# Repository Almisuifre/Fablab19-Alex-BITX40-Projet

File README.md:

# Fablab19-Alex-BITX40-Projet
Projet radio amateur fait au Fablab 19 - Création du BITX40

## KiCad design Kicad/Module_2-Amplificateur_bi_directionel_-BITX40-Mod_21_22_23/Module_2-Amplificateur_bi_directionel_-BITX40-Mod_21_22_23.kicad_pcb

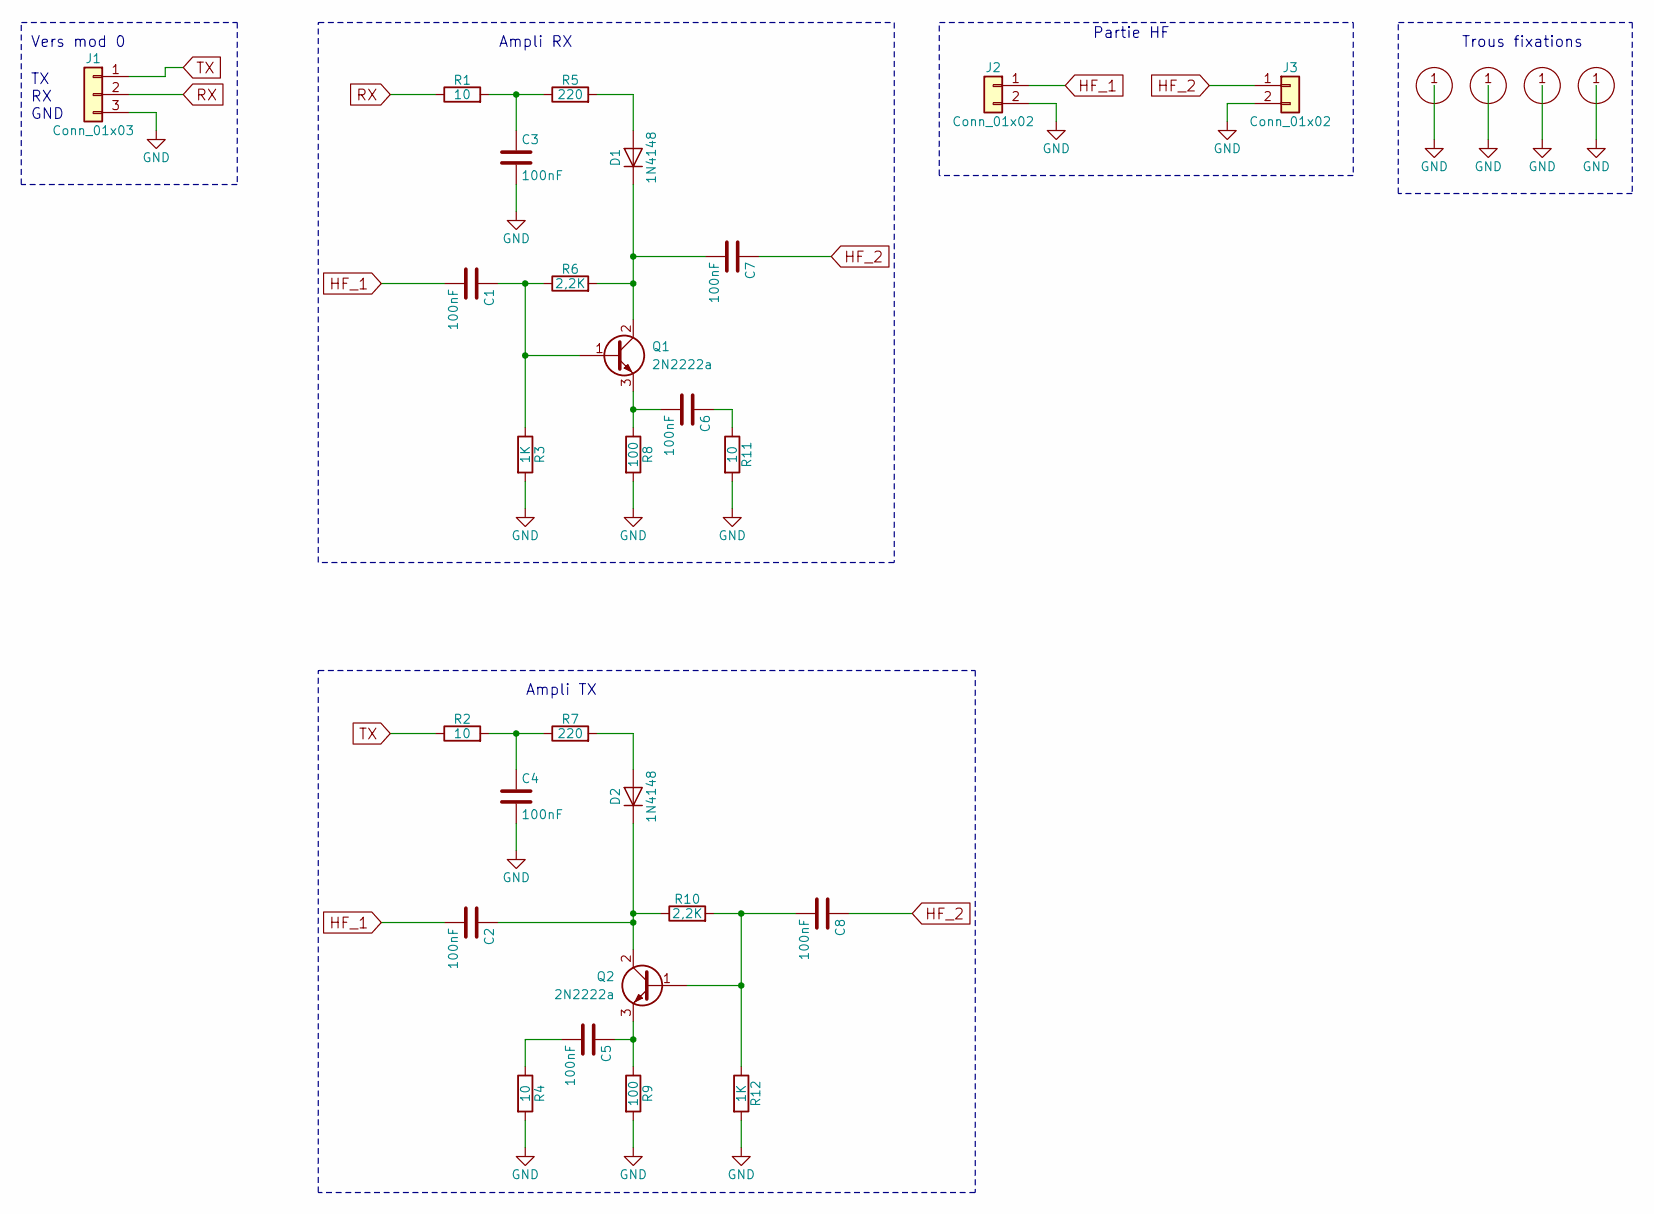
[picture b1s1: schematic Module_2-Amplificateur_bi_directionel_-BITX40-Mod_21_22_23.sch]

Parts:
C1, C2, C3, C4, C5, C6, C7, C8: 100nF; C-P_5.08-L_7.5-H_6-P_2.5
D1, D2: 1N4148; D_DO-35_SOD27_P12.70mm_Horizontal
H1, H2, H3, H4: M3-Hole
J1: Conn_01x03; Connect-3pin
J2, J3: Conn_01x02; Connect-2pin
Q1, Q2: 2N2222a; TO-18-3
R1, R2, R4, R11: 10; R_Axial_Long6.3mm_Dia2.5mm_Pas15.24mm_Horizontal
R3, R12: 1K; R_Axial_Long6.3mm_Dia2.5mm_Pas15.24mm_Horizontal
R5, R7: 220; R_Axial_Long6.3mm_Dia2.5mm_Pas15.24mm_Horizontal
R6, R10: 2,2K; R_Axial_Long6.3mm_Dia2.5mm_Pas15.24mm_Horizontal
R8, R9: 100; R_Axial_Long6.3mm_Dia2.5mm_Pas15.24mm_Horizontal

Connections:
GND: C3.2, C4.2, H1.1, H2.1, H3.1, H4.1, J1.3, J2.2, J3.2, R3.2, R4.2, R8.2, R9.2, R11.2, R12.2
HF_1: C1.2, C2.2, J2.1
HF_2: C7.1, C8.1, J3.1
unnamed: C1.1, Q1.1 (B), R3.1, R6.1
unnamed: C2.1, D2.1 (K), Q2.2 (C), R10.1
unnamed: C3.1, R1.2, R5.1
unnamed: C4.1, R2.2, R7.1
unnamed: C5.1, Q2.3 (E), R9.1
unnamed: C5.2, R4.1
unnamed: C6.1, R11.1
unnamed: C6.2, Q1.3 (E), R8.1
unnamed: C7.2, D1.1 (K), Q1.2 (C), R6.2
unnamed: C8.2, Q2.1 (B), R10.2, R12.1
unnamed: D1.2 (A), R5.2
unnamed: D2.2 (A), R7.2
RX: J1.2, R1.1
TX: J1.1, R2.1

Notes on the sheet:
TX RX GND
Vers mod 0
Partie HF
Ampli RX
Ampli TX
Trous fixations

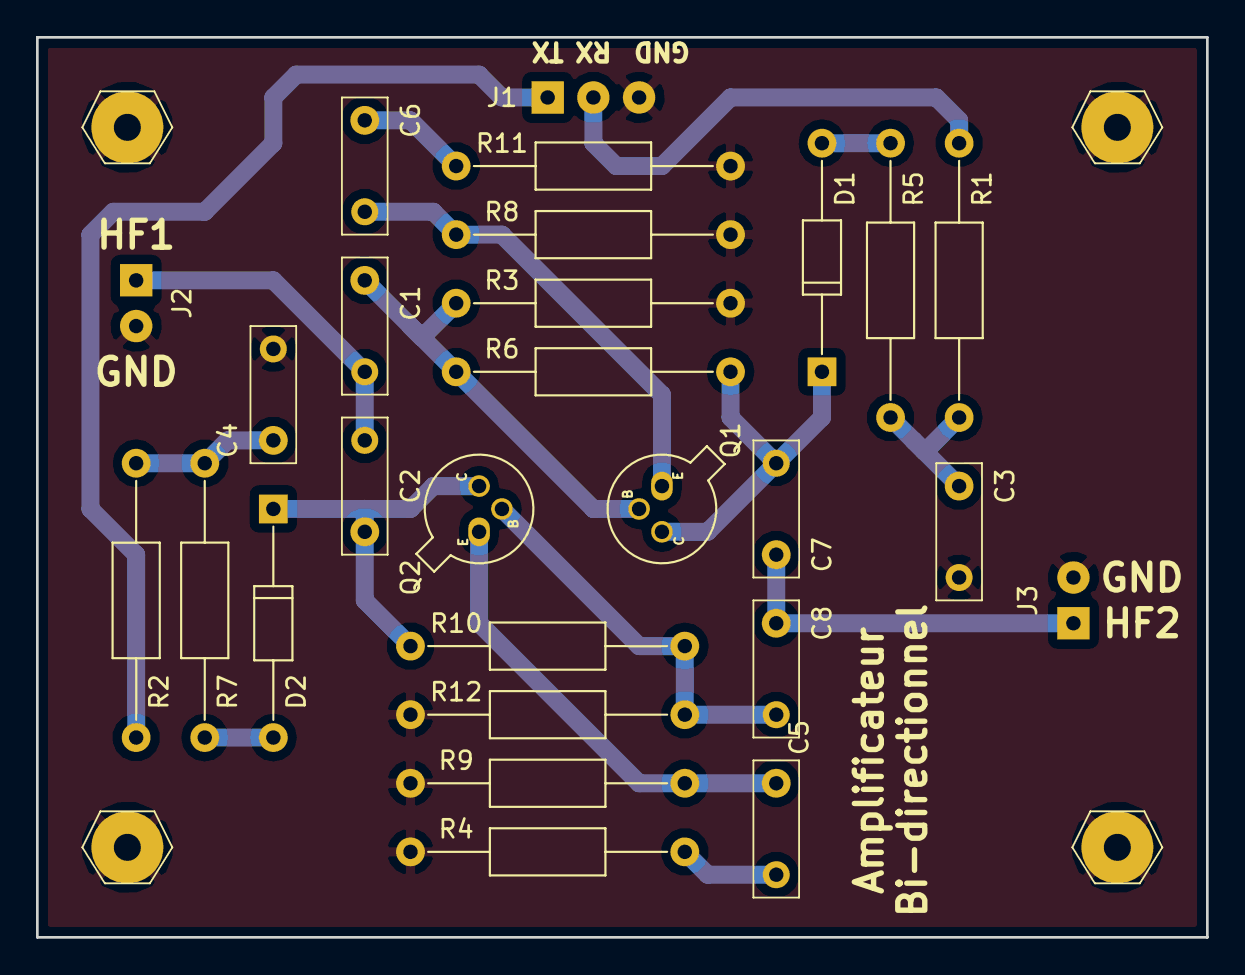
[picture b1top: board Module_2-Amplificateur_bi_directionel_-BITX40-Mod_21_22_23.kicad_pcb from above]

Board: 2 copper layers, 65.0 x 50.0 mm, 31 parts (0 on the bottom side), 17 nets.

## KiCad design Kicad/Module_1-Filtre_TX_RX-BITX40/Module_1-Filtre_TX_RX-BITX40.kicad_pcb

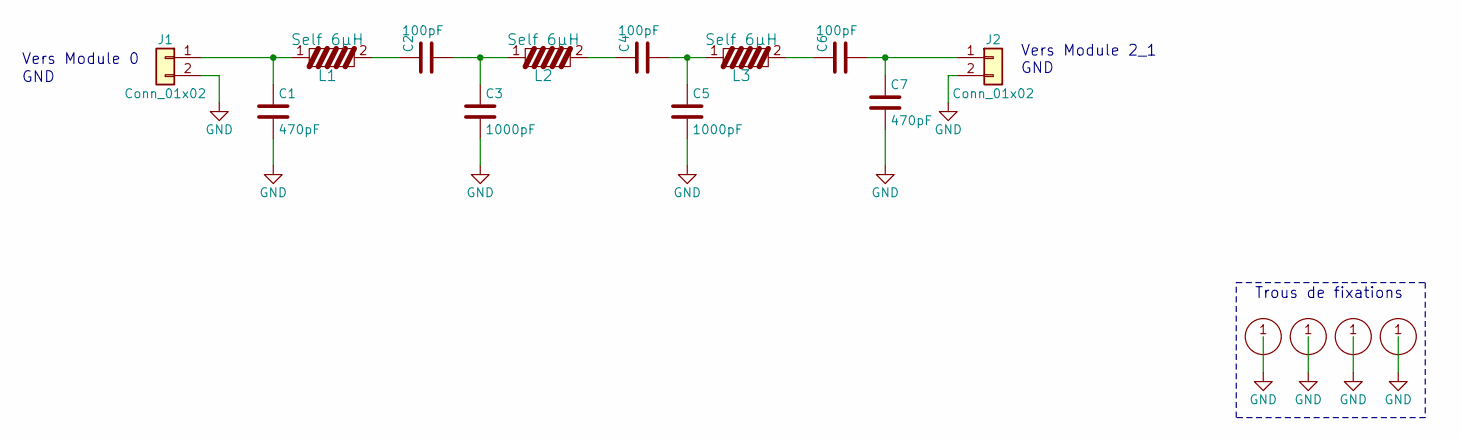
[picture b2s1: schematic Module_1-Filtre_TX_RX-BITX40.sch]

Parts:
C1, C7: 470pF; C-P_5.08-L_7.5-H_6-P_2.5
C2, C4, C6: 100pF; C-P_5.08-L_7.5-H_6-P_2.5
C3, C5: 1000pF; C-P_5.08-L_7.5-H_6-P_2.5
H1, H2, H3, H4: M3-Hole
J1, J2: Conn_01x02; Connect-2pin
L1, L2, L3: Self 6µH; Self_T30-6

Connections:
GND: C1.2, C3.2, C5.2, C7.2, H1.1, H2.1, H3.1, H4.1, J1.2, J2.2
unnamed: C1.1, J1.1, L1.1
unnamed: C2.1, L1.2
unnamed: C2.2, C3.1, L2.1
unnamed: C4.1, L2.2
unnamed: C4.2, C5.1, L3.1
unnamed: C6.1, L3.2
unnamed: C6.2, C7.1, J2.1

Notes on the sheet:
Vers Module 0
GND
Vers Module 2_1 GND
Trous de fixations

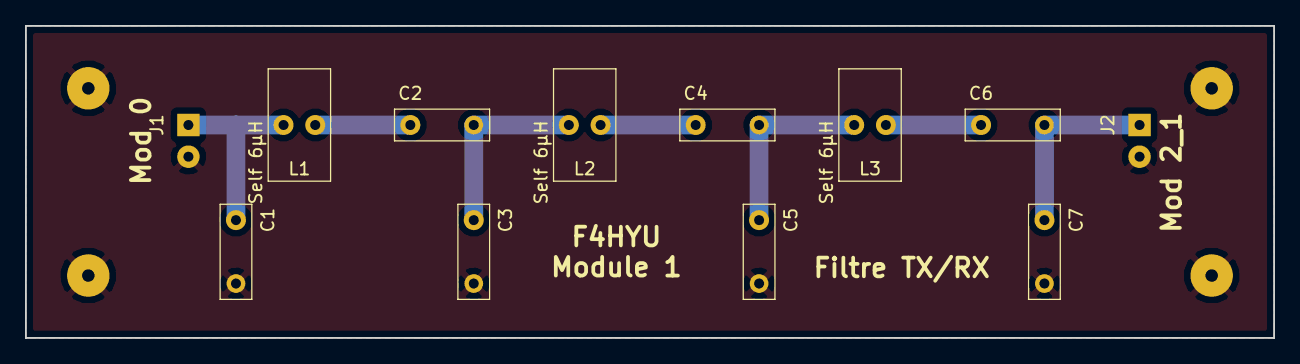
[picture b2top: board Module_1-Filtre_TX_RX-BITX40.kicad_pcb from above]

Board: 2 copper layers, 100.0 x 25.0 mm, 16 parts (0 on the bottom side), 8 nets.

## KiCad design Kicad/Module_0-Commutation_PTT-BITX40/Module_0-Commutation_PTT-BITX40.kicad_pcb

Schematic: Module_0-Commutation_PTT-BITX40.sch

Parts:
C1, C2: 10nF; C-P_5.08-L_7.5-H_6-P_2.5
C3: 100µF / 25V; CP_Radial_Dia8.0mm_Pas3.50mm
C4, C5, C6: 100nF; C-P_5.08-L_7.5-H_6-P_2.5
D1, D2: 1N4007; D_DO-41_Pas12.70mm_Horizontal
H1, H2, H3, H4: M3-Hole
J1, J2, J3, J4, J12, J13, J14, J15, J16: Conn_01x02; Connect-2pin
J5, J10, J11, J17: Conn_Coaxial; Connect-2pin
J6, J7, J8, J9, J18: Conn_01x03; Connect-3pin
K1, K2: D2n; Relais-2_NO_NC
Q1: 2N2222A; TO-18-3
Q2: 2N2907A; TO-18-3
R1, R2: 10K; R_Axial_Long6.3mm_Dia2.5mm_Pas15.24mm_Horizontal
R3, R4: 330; R_Axial_Long6.3mm_Dia2.5mm_Pas15.24mm_Horizontal
SW1, SW2, SW3: Chevron

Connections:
12V: C3.1, C4.1, C6.2, D2.1, J1.1, J3.1, J12.1, J13.1, J14.1, K2.4, K2.16
GND: C1.2, C2.2, C3.2, C4.2, C5.2, D1.2, H1.1, H2.1, H3.1, H4.1, J2.2, J3.2, J4.2, J5.2, J6.3, J7.3, J8.3, J9.3, J10.2, J11.2, J12.2, J13.2, J14.2, J15.2, J16.2, J17.2, J18.3, K1.1, Q1.3, Q2.2
unnamed: C1.1, Q1.1, R1.1
unnamed: C2.1, Q2.1, R2.1
unnamed: J1.2, R1.2
unnamed: J2.1, R2.2
unnamed: J4.1, SW1.1
unnamed: J5.1, K1.4
unnamed: J10.1, K1.8
unnamed: J11.1, K2.9
unnamed: J17.1, K2.13
unnamed: J18.1, R3.1
unnamed: J18.2, R4.1
unnamed: K1.6, K2.11
unnamed: Q1.2, SW2.1
unnamed: Q2.3, SW3.1
PTT: C6.1, D2.2, K2.1, SW1.2, SW2.2, SW3.2
RX: J6.2, J7.2, J8.2, J9.2, K2.6, R4.2
TX: C5.1, D1.1, J6.1, J7.1, J8.1, J9.1, J15.1, J16.1, K1.16, K2.8, R3.2

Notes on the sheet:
Vers l'antene
Vers Module 12 Filtre passe bande
Vers Module 10 Amplificateur Etage puissance
Vers Module 1 Filtre TX/RX
PTT+
+12V
GND
Commande positive
PTT-
Commande négative
Commande direct
PTT Direct GND
Alimentation
TX RX GND Vers Module 2-1
TX RX GND Vers Module 2-2
TX RX GND Vers Module 2-3
TX RX GND Vers Module 9
Led TX Led RX GND
12V GND Vers Module 11
12V GND Vers Module 4-1
12V GND Vers Module 4-2
TX GND Vers Module 8
TX GND Vers Module 10
Trous fixations M3

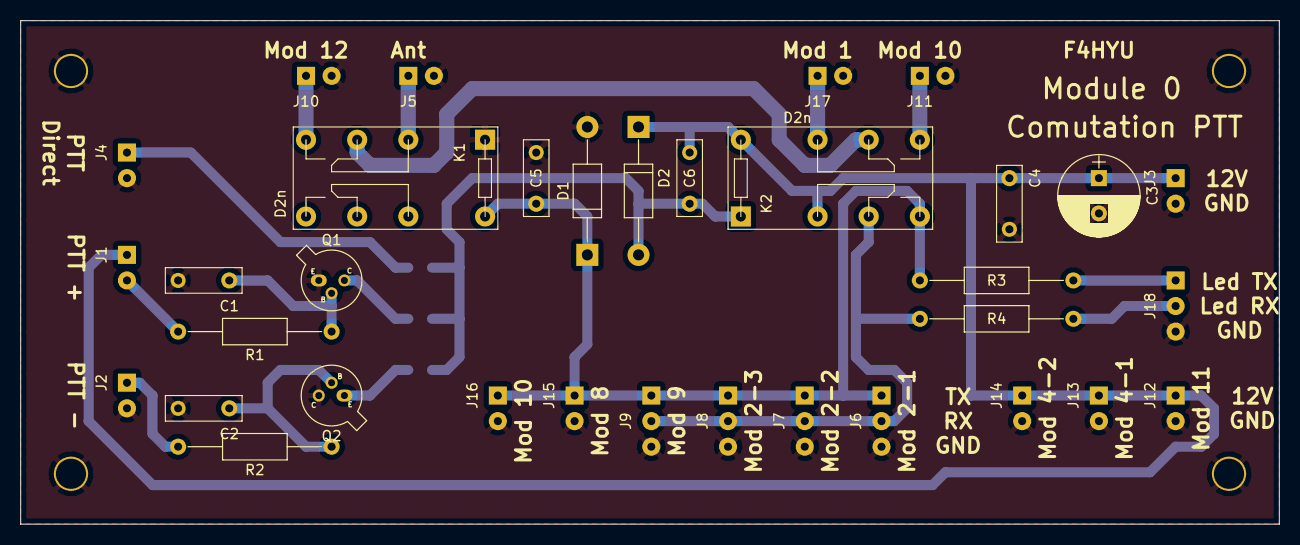
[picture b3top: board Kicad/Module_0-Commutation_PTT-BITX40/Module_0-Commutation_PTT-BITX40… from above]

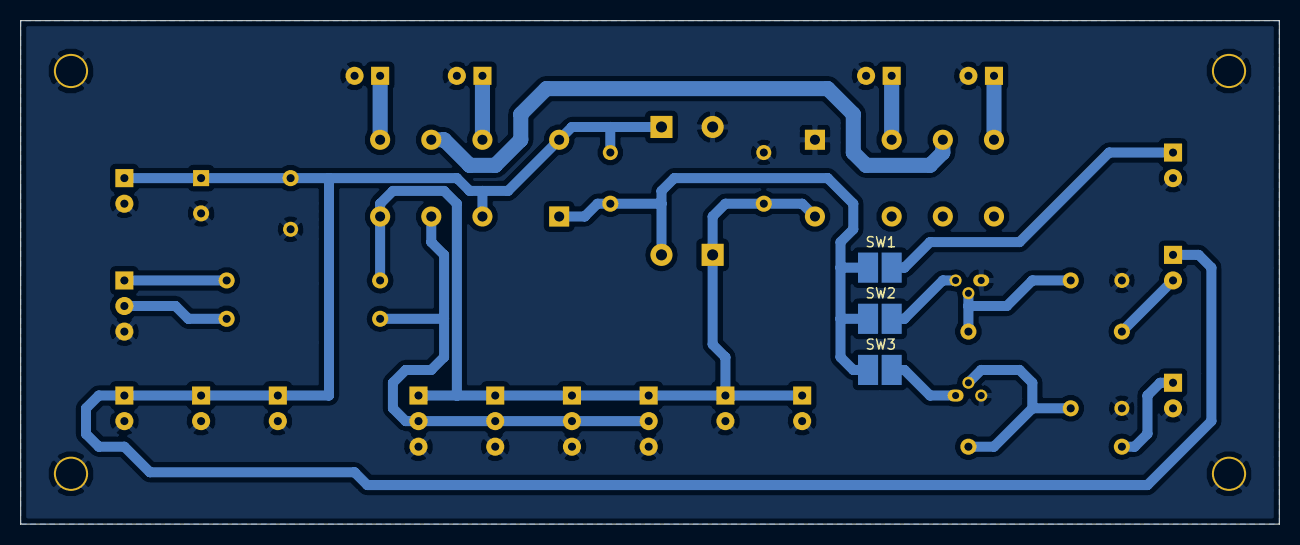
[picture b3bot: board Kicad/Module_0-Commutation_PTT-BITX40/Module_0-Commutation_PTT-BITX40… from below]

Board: 2 copper layers, 125.0 x 50.0 mm, 41 parts (3 on the bottom side), 19 nets.

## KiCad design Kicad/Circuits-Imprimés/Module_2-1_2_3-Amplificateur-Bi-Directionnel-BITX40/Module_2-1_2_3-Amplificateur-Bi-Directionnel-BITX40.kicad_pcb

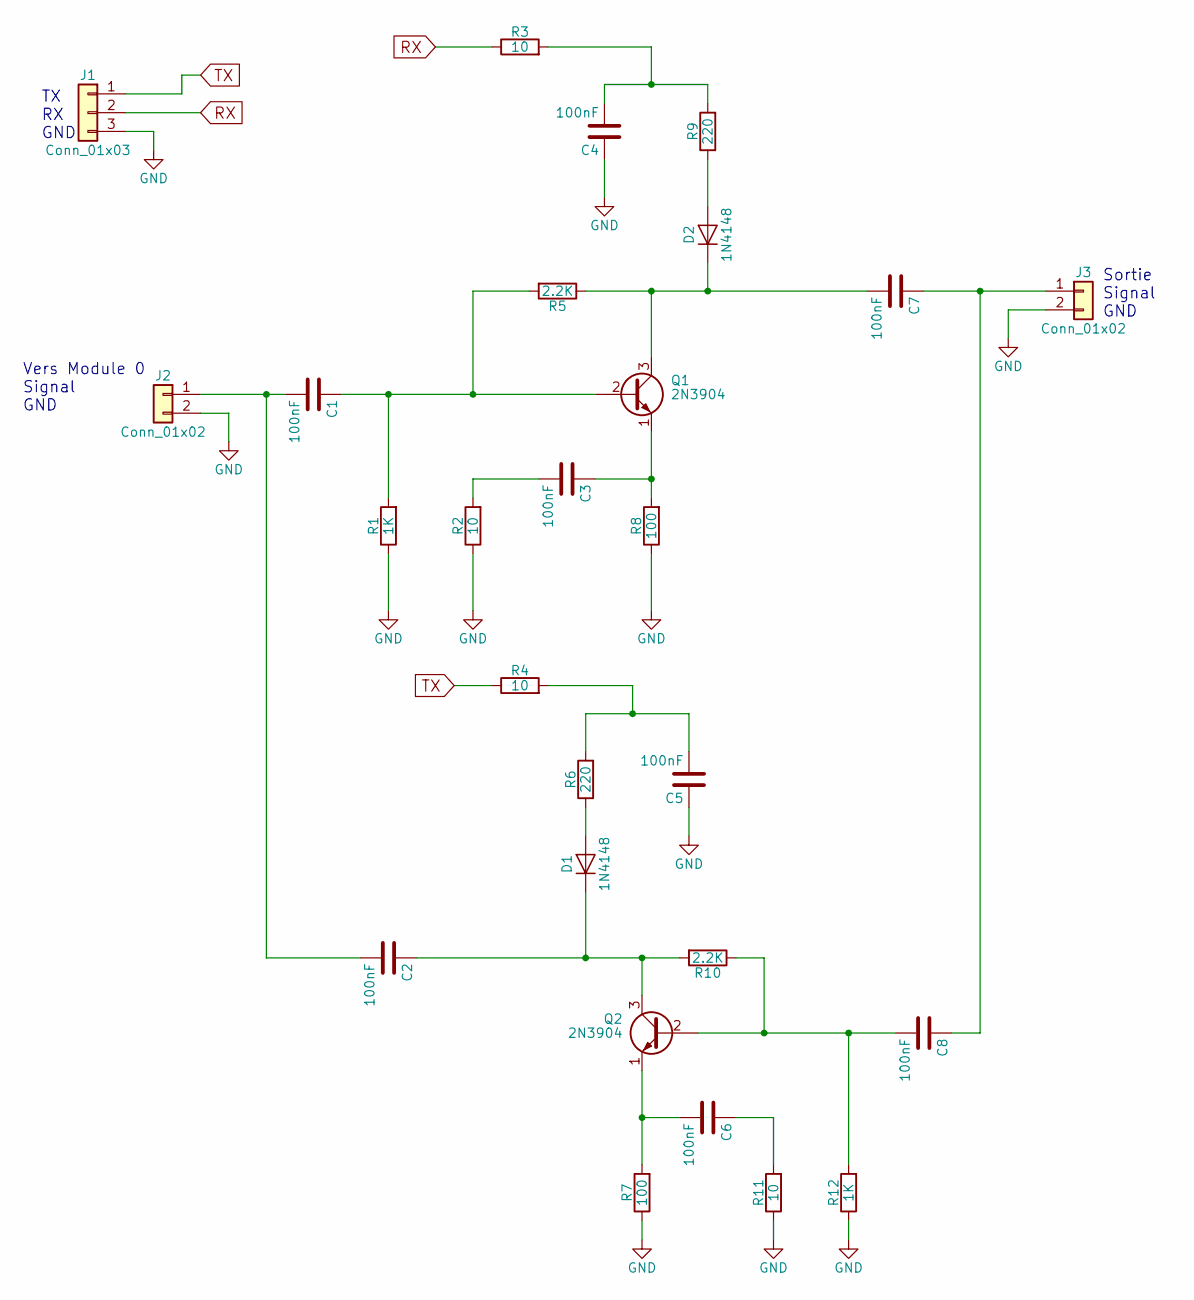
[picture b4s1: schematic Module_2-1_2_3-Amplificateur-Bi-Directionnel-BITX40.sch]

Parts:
C1, C2, C3, C4, C5, C6, C7, C8: 100nF; C_Disc_D3.8mm_W2.6mm_P2.50mm
D1, D2: 1N4148; D_DO-35_SOD27_P7.62mm_Horizontal
J1: Conn_01x03; Connect-3pin
J2, J3: Conn_01x02; Connect-2pin
Q1, Q2: 2N3904; TO-92_Molded_Narrow
R1, R12: 1K; R_Axial_DIN0204_L3.6mm_D1.6mm_P5.08mm_Horizontal
R2, R3, R4, R11: 10; R_Axial_DIN0204_L3.6mm_D1.6mm_P5.08mm_Horizontal
R5, R10: 2.2K; R_Axial_DIN0204_L3.6mm_D1.6mm_P5.08mm_Horizontal
R6, R9: 220; R_Axial_DIN0204_L3.6mm_D1.6mm_P5.08mm_Horizontal
R7, R8: 100; R_Axial_DIN0204_L3.6mm_D1.6mm_P5.08mm_Horizontal

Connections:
GND: C4.1, C5.1, J1.3, J2.2, J3.2, R1.1, R2.1, R7.1, R8.1, R11.1, R12.1
unnamed: C1.1, Q1.2 (B), R1.2, R5.2
unnamed: C1.2, C2.2, J2.1
unnamed: C2.1, D1.1 (K), Q2.3 (C), R10.2
unnamed: C3.1, Q1.1 (E), R8.2
unnamed: C3.2, R2.2
unnamed: C4.2, R3.2, R9.2
unnamed: C5.2, R4.2, R6.2
unnamed: C6.1, R11.2
unnamed: C6.2, Q2.1 (E), R7.2
unnamed: C7.1, C8.1, J3.1
unnamed: C7.2, D2.1 (K), Q1.3 (C), R5.1
unnamed: C8.2, Q2.2 (B), R10.1, R12.2
unnamed: D1.2 (A), R6.1
unnamed: D2.2 (A), R9.1
RX: J1.2, R3.1
TX: J1.1, R4.1

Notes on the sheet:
TX RX GND
Vers Module 0 Signal GND
Sortie Signal GND

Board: 2 copper layers, 27 parts (0 on the bottom side), 17 nets, no tracks yet.

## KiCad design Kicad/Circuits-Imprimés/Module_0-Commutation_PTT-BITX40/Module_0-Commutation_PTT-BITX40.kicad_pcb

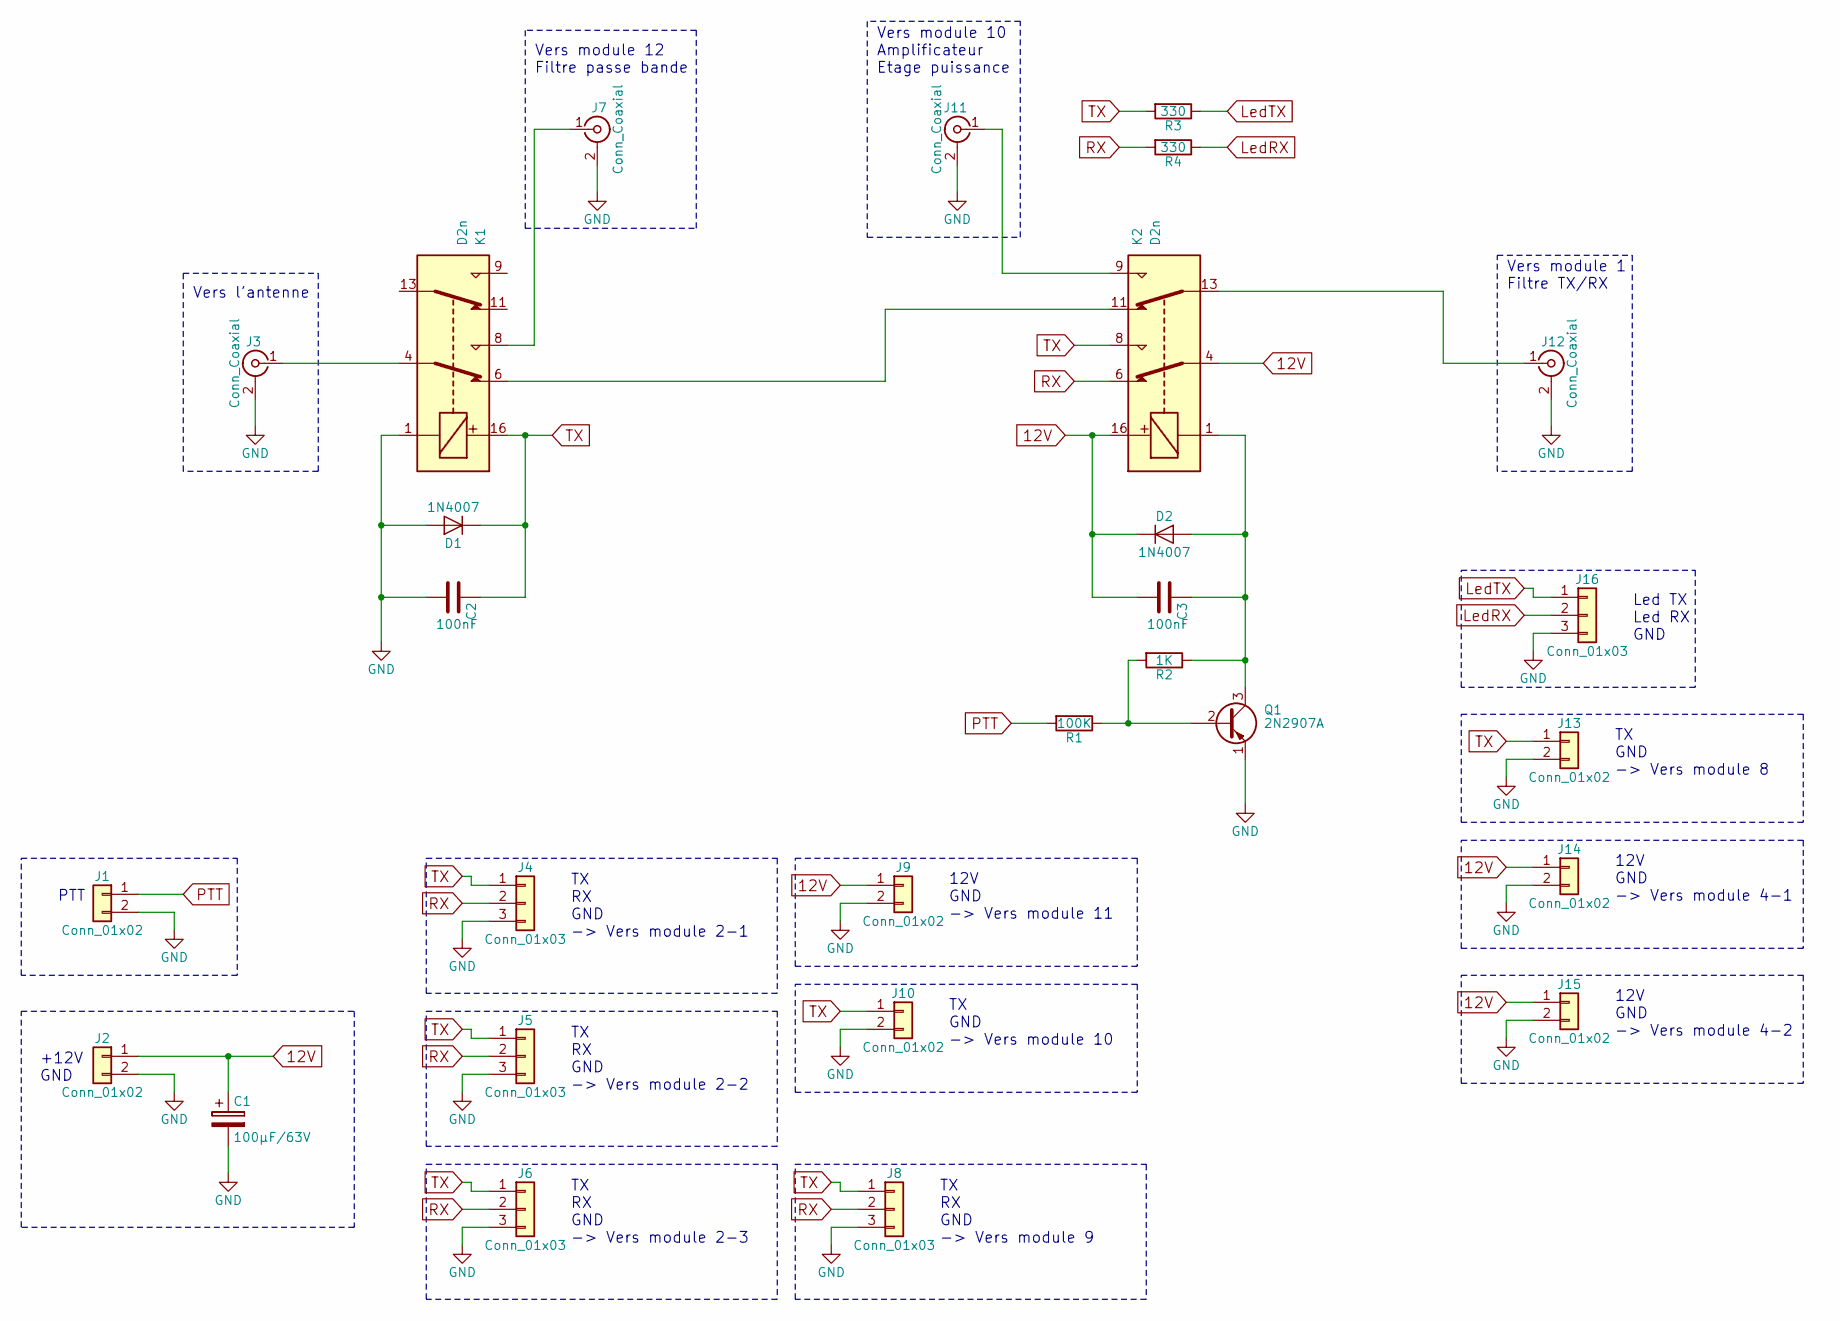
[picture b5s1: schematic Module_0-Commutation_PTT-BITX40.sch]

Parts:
C1: 100µF/63V; CP_Radial_D5.0mm_P2.50mm
C2, C3: 100nF; C_Disc_D5.0mm_W2.5mm_P2.50mm
D1, D2: 1N4007; D_A-405_P10.16mm_Horizontal
J1, J2, J9, J10, J13, J14, J15: Conn_01x02; Connect-2pin
J3, J7, J11, J12: Conn_Coaxial; Connect-2pin
J4, J5, J6, J8, J16: Conn_01x03; Connect-3pin
K1, K2: D2n; Relais-2_NO_NC
Q1: 2N2907A; TO-18-3
R1: 100K; R_Axial_DIN0204_L3.6mm_D1.6mm_P7.62mm_Horizontal
R2: 1K; R_Axial_DIN0204_L3.6mm_D1.6mm_P7.62mm_Horizontal
R3, R4: 330; R_Axial_DIN0204_L3.6mm_D1.6mm_P7.62mm_Horizontal

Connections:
12V: C1.1, C3.2, D2.1 (K), J2.1, J9.1, J14.1, J15.1, K2.4, K2.16
GND: C1.2, C2.2, D1.2 (A), J1.2, J2.2, J3.2 (Ext), J4.3, J5.3, J6.3, J7.2 (Ext), J8.3, J9.2, J10.2, J11.2 (Ext), J12.2 (Ext), J13.2, J14.2, J15.2, J16.3, K1.1, Q1.1 (E)
LedRX: J16.2, R4.1
LedTX: J16.1, R3.1
unnamed: C3.1, D2.2 (A), K2.1, Q1.3 (C), R2.1
unnamed: J3.1 (In), K1.4
unnamed: J7.1 (In), K1.8
unnamed: J11.1 (In), K2.9
unnamed: J12.1 (In), K2.13
unnamed: K1.6, K2.11
unnamed: Q1.2 (B), R1.1, R2.2
PTT: J1.1, R1.2
RX: J4.2, J5.2, J6.2, J8.2, K2.6, R4.2
TX: C2.1, D1.1 (K), J4.1, J5.1, J6.1, J8.1, J10.1, J13.1, K1.16, K2.8, R3.2

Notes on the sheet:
Vers l'antenne
Vers module 12 Filtre passe bande
Vers module 10 Amplificateur Etage puissance
Vers module 1 Filtre TX/RX
+12V GND
PTT
TX RX GND -> Vers module 2-1
TX RX GND -> Vers module 2-2
TX RX GND -> Vers module 2-3
12V GND -> Vers module 4-1
12V GND -> Vers module 4-2
TX GND -> Vers module 8
TX RX GND -> Vers module 9
TX GND -> Vers module 10
12V GND -> Vers module 11
Led TX Led RX GND

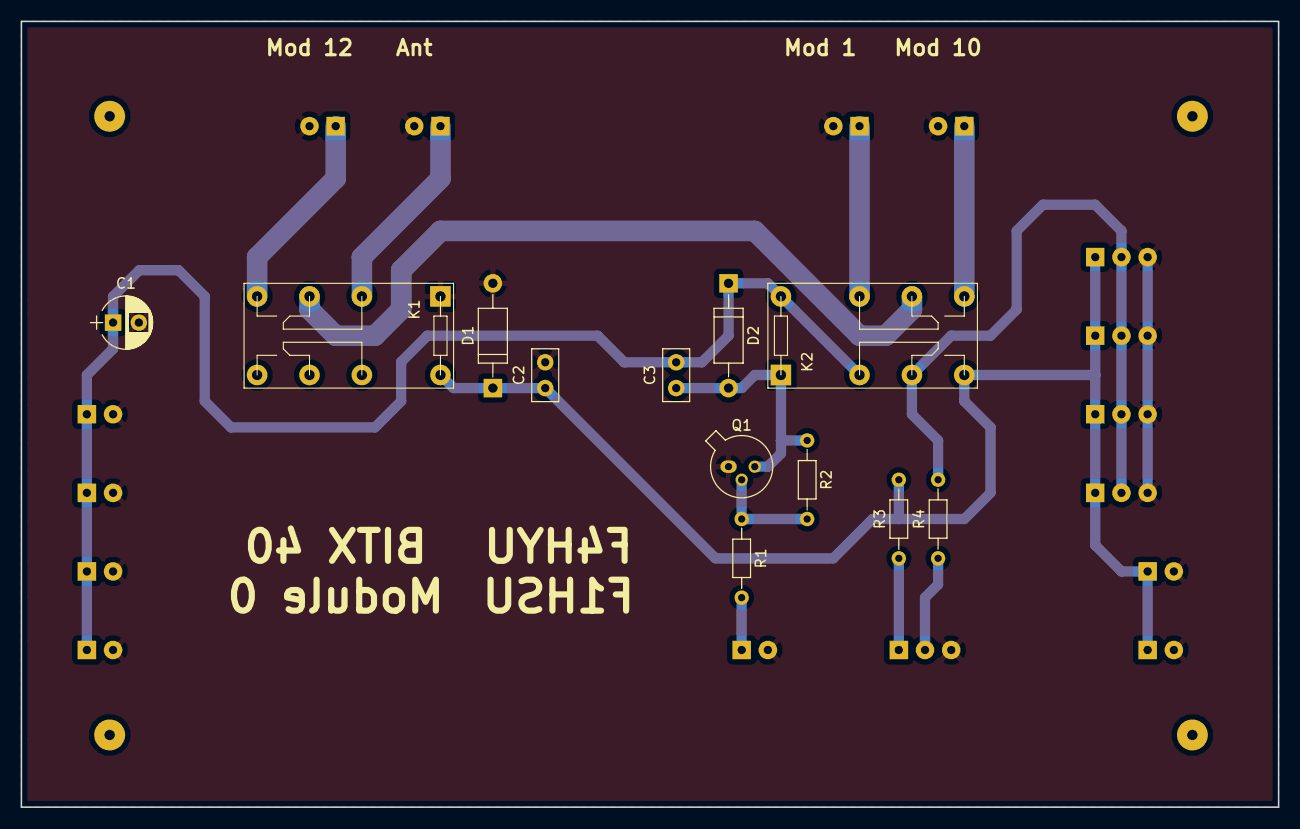
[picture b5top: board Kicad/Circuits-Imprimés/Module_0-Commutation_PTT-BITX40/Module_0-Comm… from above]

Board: 2 copper layers, 121.9 x 76.2 mm, 28 parts (0 on the bottom side), 14 nets.

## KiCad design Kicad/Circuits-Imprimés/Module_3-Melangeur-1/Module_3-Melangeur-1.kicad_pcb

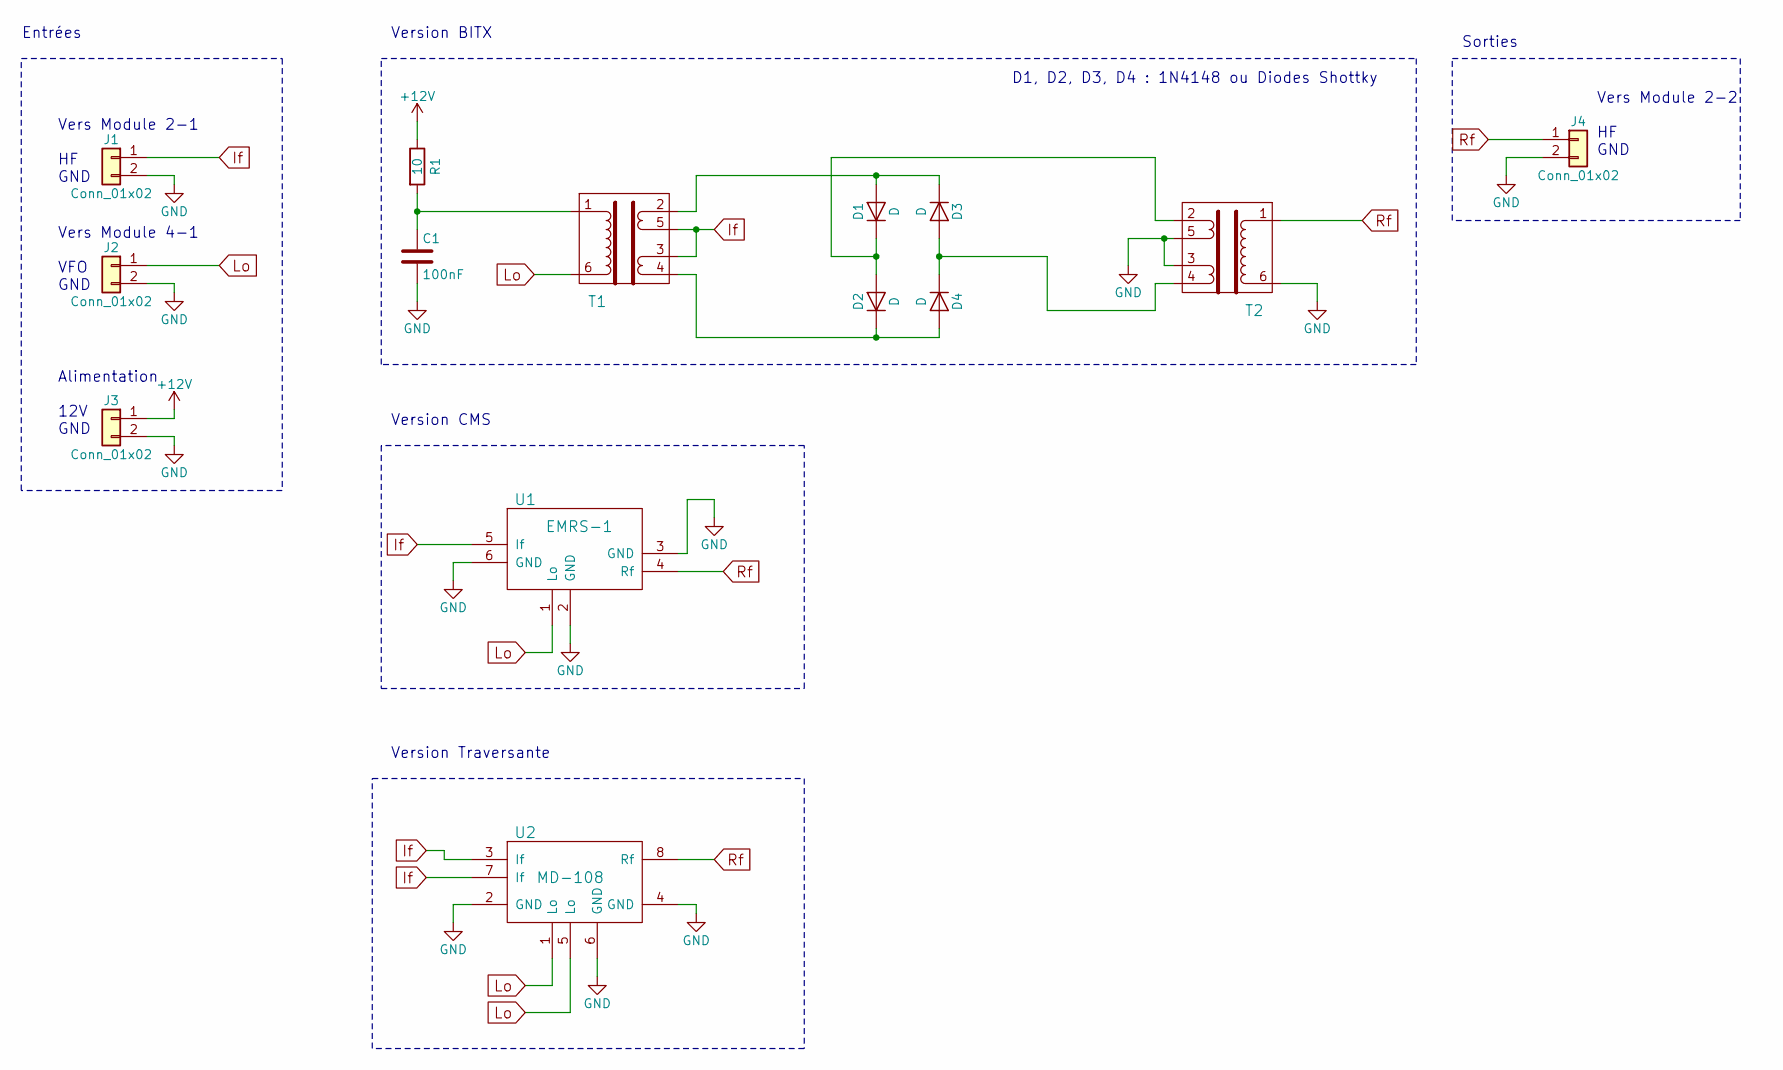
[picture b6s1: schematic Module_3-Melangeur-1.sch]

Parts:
C1: 100nF; C_Disc_D3.8mm_W2.6mm_P2.50mm
D1, D2, D3, D4: D; D_DO-35_SOD27_P7.62mm_Horizontal
J1, J2, J3, J4: Conn_01x02; Connect-2pin
R1: 10; R_Axial_DIN0204_L3.6mm_D1.6mm_P7.62mm_Horizontal
T1, T2: Transformateur; Transformateur-T37-43
U1: EMRS-1
U2: MD-108

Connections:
+12V: J3.1, R1.1
GND: C1.2, J1.2, J2.2, J3.2, J4.2, T2.3, T2.5, T2.6, U1.2 (GND), U1.3 (GND), U1.6 (GND), U2.2 (GND), U2.4 (GND), U2.6 (GND)
If: J1.1, T1.3, T1.5, U1.5 (If), U2.3 (If), U2.7 (If)
Lo: J2.1, T1.6, U1.1 (Lo), U2.1 (Lo), U2.5 (Lo)
unnamed: C1.1, R1.2, T1.1
unnamed: D1.1 (K), D2.2 (A), T2.2
unnamed: D1.2 (A), D3.1 (K), T1.2
unnamed: D2.1 (K), D4.2 (A), T1.4
unnamed: D3.2 (A), D4.1 (K), T2.4
Rf: J4.1, T2.1, U1.4 (Rf), U2.8 (Rf)

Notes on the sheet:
Vers Module 2-1 HF GND
Vers Module 4-1 VFO GND
Vers Module 2-2 HF GND
Alimentation 12V GND
Sorties
Version BITX
Version CMS
Version Traversante
Entrées
D1, D2, D3, D4 : 1N4148 ou Diodes Shottky

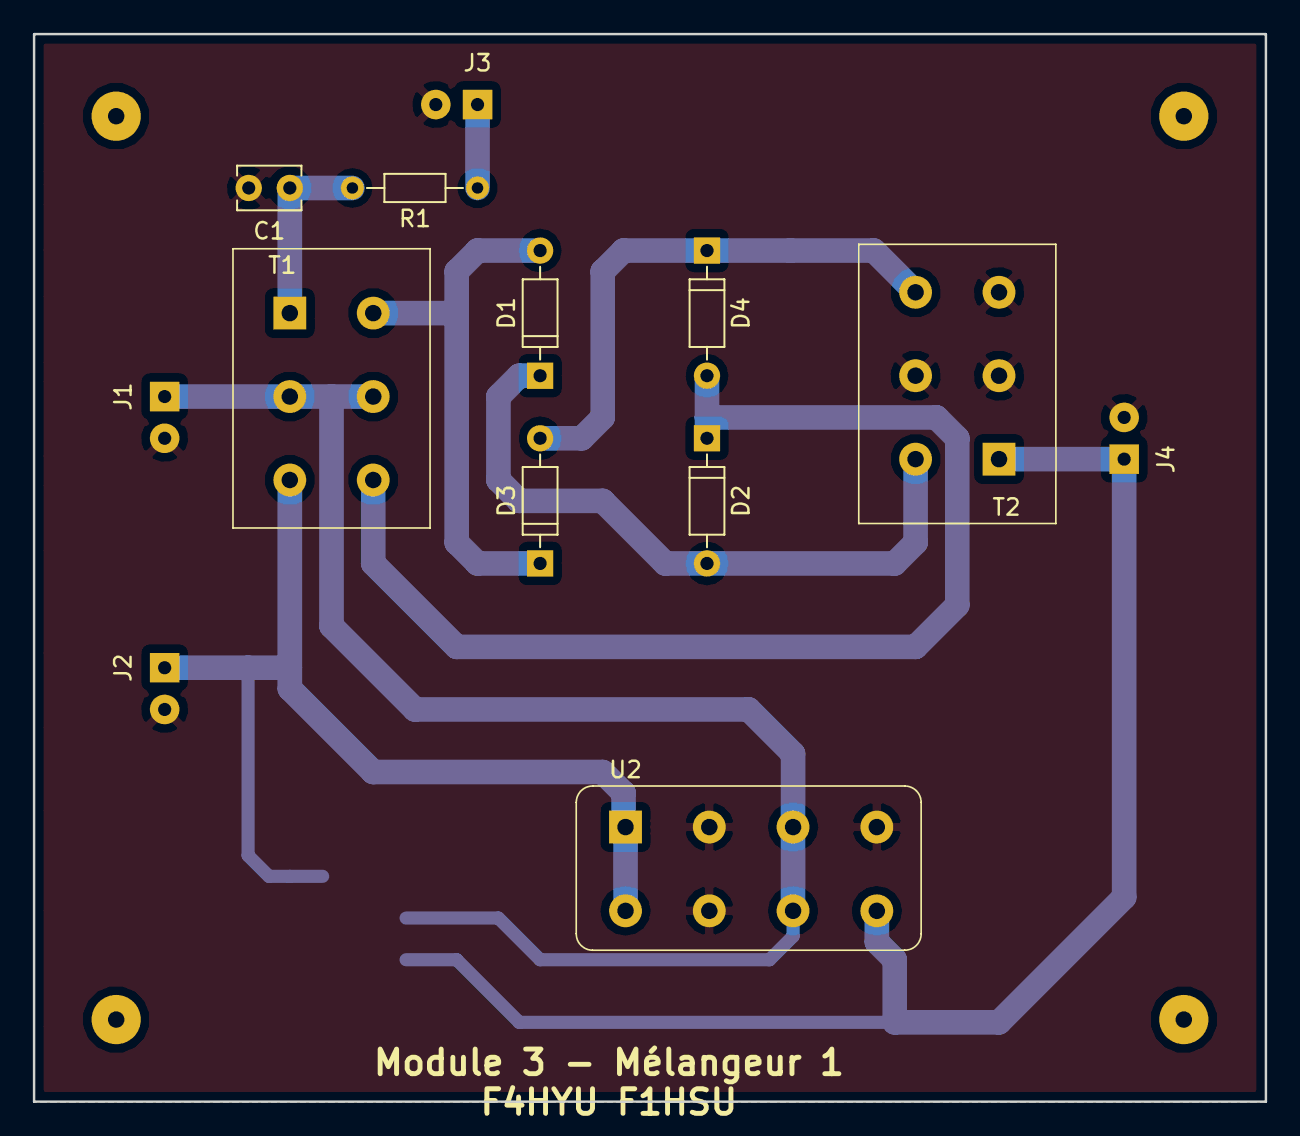
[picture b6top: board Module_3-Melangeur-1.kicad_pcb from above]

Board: 2 copper layers, 75.0 x 65.0 mm, 14 parts (1 on the bottom side), 10 nets.

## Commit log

2018-02-10 Create projet BITX 40 from Kicad
    Create projet BITX 40 from Kicad
2018-02-10 Update project BITX 40
    Update project BITX 40
2018-02-10 Update project BITX
    Update project BITX 40. Add new hole. New version PCB.
2018-02-10 Update project
    Update project
2018-02-11 Update project - Add gerber file
    Add gerber file into the project BITX 40.
2018-02-11 Add Filter TX/RX - Module 1 in BITX 40
    Add filter bi-directionnal. This Module 1 in BITX 40.
2018-02-11 Add an image
    Add an image
2018-02-13 Update filter -module 1
    Update module 1
    - New assignment cellule in filter
2018-02-19 Update Module 2
    Create PCB on Module 2-X.
    Add resistor and update position TX/RX in schematic.
2018-02-22 Update project
    Update project. Clean export Kicad and new view PCB 3D
2018-02-25 Update project - new RF Mixer
    Update project
    - Update link of 3d Shapes
    - Implant a new PCB Module 3 RF Mixer
2018-02-26 Update hole to the module 3 RF Mixer
    Update Hole for the module 3 - RF Mixer
2018-02-26 Update wrong cuting ouside
    Updage cuting outside in module 3
2018-02-26 Update Module 3 Optimise GND
    Update Module 3:
    New GND Optimised in PCB Bottom
2018-03-01 Update
    Update
2018-03-22 Delete project
    Problem soldering and mount component. Reinit the project and new organize.
2018-03-24 Add Module 0
    Add New module
2018-03-26 Update missing PTT-
    Missing PNP mount PTT- are changed
    PTT+ not use GND. Update for the 12V command.
2018-04-29 New module
    Module 2 are created.
    Use Module 2.1, 2.2, 2.3
2018-06-12 Update
    Update amplificateur.
    Problem route PCB -> Corrected.
    Reduce weight PCB -> Corrected.
2019-04-06 Update information et liens
    Update information et liens
2019-07-18 Commit
    Commit
